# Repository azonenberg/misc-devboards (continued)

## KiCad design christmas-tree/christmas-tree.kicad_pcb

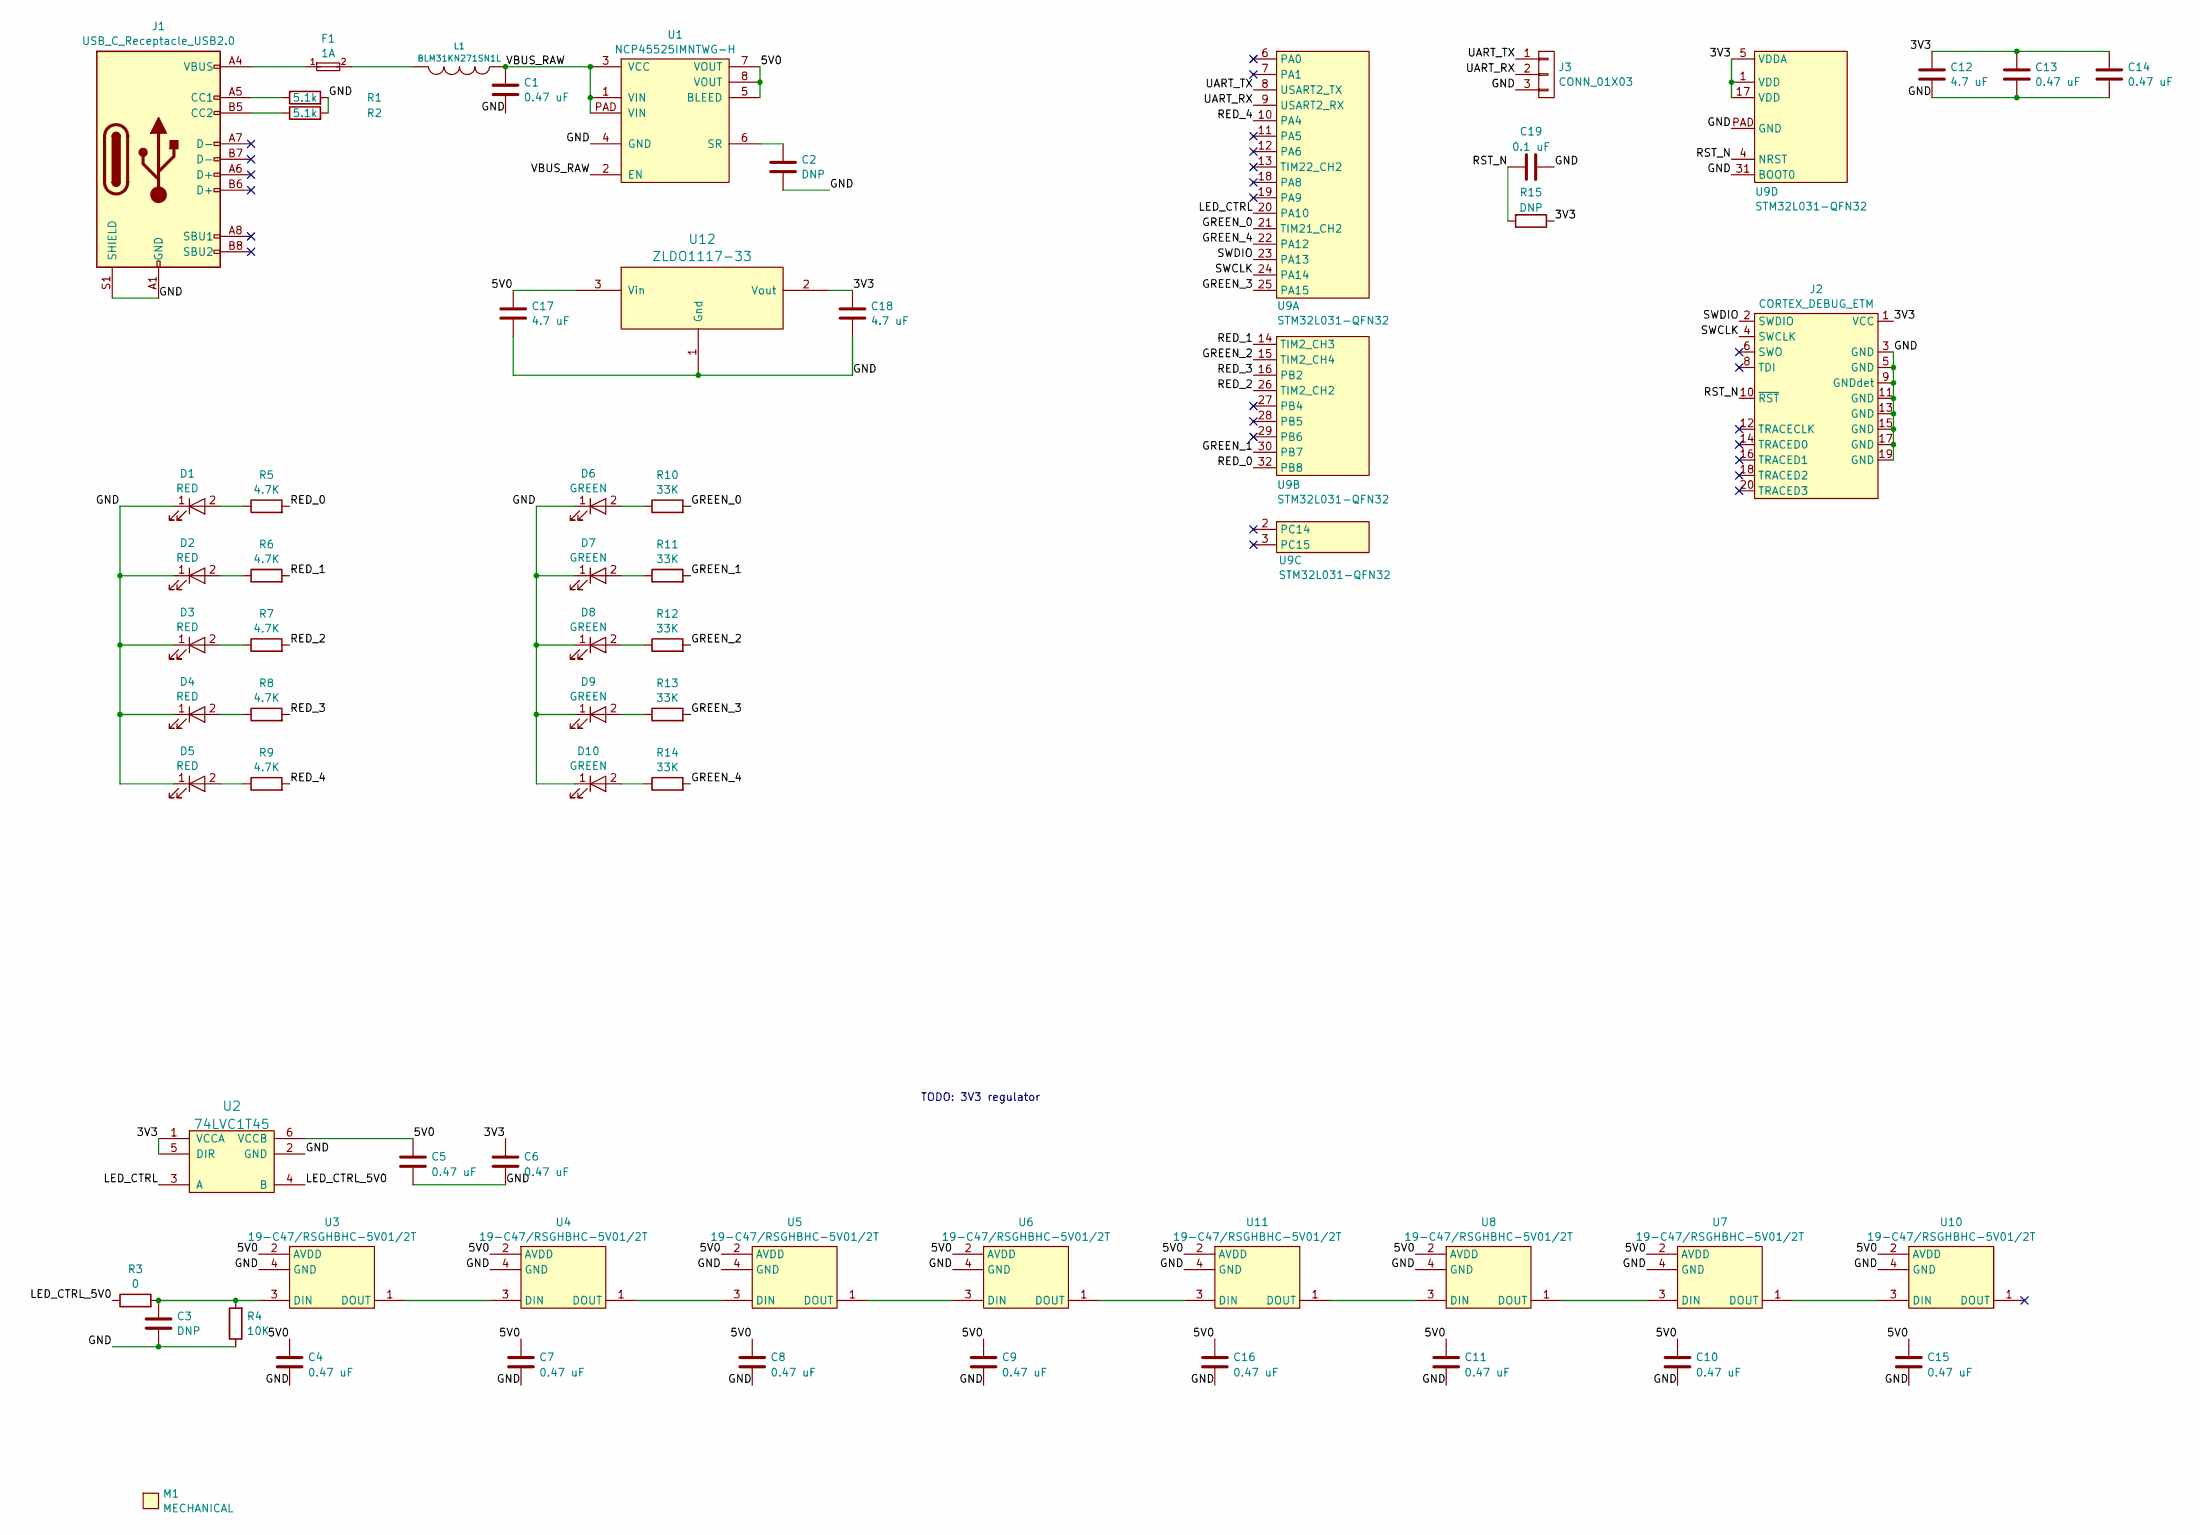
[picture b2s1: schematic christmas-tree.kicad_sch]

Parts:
C1, C4, C5, C6, C7, C8, C9, C10, C11, C13, C14, C15, C16: 0.47 uF; EIA_0402_CAP_NOSILK
C2, C3: DNP; EIA_0402_CAP_NOSILK
C12, C17, C18: 4.7 uF; EIA_0603_CAP_NOSILK
C19: 0.1 uF; EIA_0402_CAP_NOSILK
D1, D2, D3, D4, D5: RED; EIA_0402_LED
D6, D7, D8, D9, D10: GREEN; EIA_0402_LED
F1: 1A; EIA_0402_RES_NOSILK
J1: USB_C_Receptacle_USB2.0; USB_C_Receptacle_HRO_TYPE-C-31-M-12
J2: CORTEX_DEBUG_ETM; CONN_HEADER_1.27MM_2x10_SMT_SAMTEC_FTSH-110-01-L-DV-K
J3: CONN_01X03; CONN_HEADER_2.54MM_1x3_REFLOW
L1: BLM31KN271SN1L; EIA_1206_CAP_NOSILK
M1: MECHANICAL; MECHANICAL_CLEARANCEHOLE_4_40
R1, R2: 5.1k; EIA_0402_RES_NOSILK
R3: 0; EIA_0402_RES_NOSILK
R4: 10K; EIA_0402_RES_NOSILK
R5, R6, R7, R8, R9: 4.7K; EIA_0402_RES_NOSILK
R10, R11, R12, R13, R14: 33K; EIA_0402_RES_NOSILK
R15: DNP; EIA_0402_RES_NOSILK
U1: NCP45525IMNTWG-H; DFN_8_0.5MM_2x2MM
U2: 74LVC1T45; DFN_6_0.5MM_1.6x1.6MM_TI_DPK
U3, U4, U5, U6, U7, U8, U10, U11: 19-C47/RSGHBHC-5V01/2T; LED_EVERLIGHT_19-C47_RSGHBHC-5V01_2T
U9: STM32L031-QFN32; QFN_32_0.5MM_5x5MM
U12: ZLDO1117-33; SOT223-4

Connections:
/3V3: C6.1, C12.1, C13.1, C14.1, C18.1, J2.1 (VCC), R15.1, U2.1 (VCCA), U2.5 (DIR), U9.1 (VDD), U9.5 (VDDA), U9.17 (VDD), U12.2 (Vout)
/5V0: C4.1, C5.1, C7.1, C8.1, C9.1, C10.1, C11.1, C15.1, C16.1, C17.1, U1.5 (BLEED), U1.7 (VOUT), U1.8 (VOUT), U2.6 (VCCB), U3.2 (AVDD), U4.2 (AVDD), U5.2 (AVDD), U6.2 (AVDD), U7.2 (AVDD), U8.2 (AVDD), U10.2 (AVDD), U11.2 (AVDD), U12.3 (Vin)
/GND: C1.2, C2.2, C3.2, C4.2, C5.2, C6.2, C7.2, C8.2, C9.2, C10.2, C11.2, C12.2, C13.2, C14.2, C15.2, C16.2, C17.2, C18.2, C19.2, D1.1 (K), D2.1 (K), D3.1 (K), D4.1 (K), D5.1 (K), D6.1 (K), D7.1 (K), D8.1 (K), D9.1 (K), D10.1 (K), J1.A1 (GND), J1.A12 (GND), J1.B1 (GND), J1.B12 (GND), J1.S1 (SHIELD), J2.3 (GND), J2.5 (GND), J2.9 (GNDdet), J2.11 (GND), J2.13 (GND), J2.15 (GND), J2.17 (GND), J2.19 (GND), J3.3, R1.2, R2.2, R4.1, U1.4 (GND), U2.2 (GND), U3.4 (GND), U4.4 (GND), U5.4 (GND), U6.4 (GND), U7.4 (GND), U8.4 (GND), U9.31 (BOOT0), U9.PAD (GND), U10.4 (GND), U11.4 (GND), U12.1 (Gnd)
/GREEN_0: R10.2, U9.21 (TIM21_CH2)
/GREEN_1: R11.2, U9.30 (PB7)
/GREEN_2: R12.2, U9.15 (TIM2_CH4)
/GREEN_3: R13.2, U9.25 (PA15)
/GREEN_4: R14.2, U9.22 (PA12)
/LED_CTRL: U2.3 (A), U9.20 (PA10)
/LED_CTRL_5V0: R3.1, U2.4 (B)
/RED_0: R5.2, U9.32 (PB8)
/RED_1: R6.2, U9.14 (TIM2_CH3)
/RED_2: R7.2, U9.26 (TIM2_CH2)
/RED_3: R8.2, U9.16 (PB2)
/RED_4: R9.2, U9.10 (PA4)
/RST_N: C19.1, J2.10 (~RST), R15.2, U9.4 (NRST)
/SWCLK: J2.4 (SWCLK), U9.24 (PA14)
/SWDIO: J2.2 (SWDIO), U9.23 (PA13)
/UART_RX: J3.2, U9.9 (USART2_RX)
/UART_TX: J3.1, U9.8 (USART2_TX)
/VBUS_RAW: C1.1, L1.1, U1.1 (VIN), U1.2 (EN), U1.3 (VCC), U1.PAD (VIN)
unnamed: D1.2 (A), R5.1
unnamed: D2.2 (A), R6.1
unnamed: D3.2 (A), R7.1
unnamed: D4.2 (A), R8.1
unnamed: D5.2 (A), R9.1
unnamed: D6.2 (A), R10.1
unnamed: D7.2 (A), R11.1
unnamed: D8.2 (A), R12.1
unnamed: D9.2 (A), R13.1
unnamed: D10.2 (A), R14.1
unnamed: F1.1, J1.A4 (VBUS), J1.A9 (VBUS), J1.B4 (VBUS), J1.B9 (VBUS)
unnamed: F1.2, L1.2
unnamed: J1.A5 (CC1), R1.1
unnamed: J1.B5 (CC2), R2.1
unnamed: C2.1, U1.6 (SR)
unnamed: C3.1, R3.2, R4.2, U3.3 (DIN)
unnamed: U3.1 (DOUT), U4.3 (DIN)
unnamed: U4.1 (DOUT), U5.3 (DIN)
unnamed: U5.1 (DOUT), U6.3 (DIN)
unnamed: U7.3 (DIN), U8.1 (DOUT)
unnamed: U7.1 (DOUT), U10.3 (DIN)
unnamed: U6.1 (DOUT), U11.3 (DIN)
unnamed: U8.3 (DIN), U11.1 (DOUT)

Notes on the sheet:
TODO: 3V3 regulator

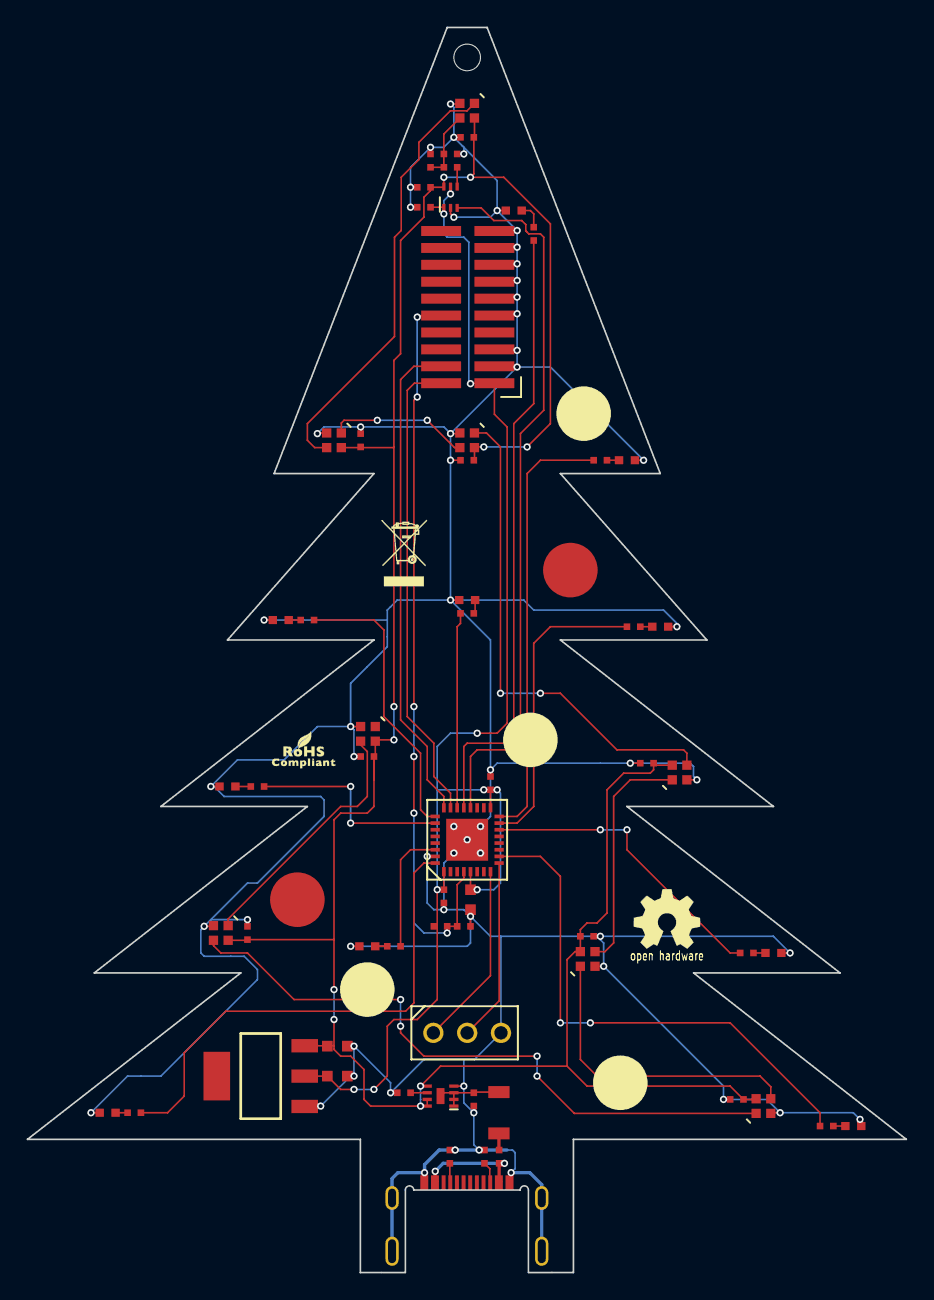
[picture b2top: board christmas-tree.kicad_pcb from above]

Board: 2 copper layers, 66.0 x 93.5 mm, 62 parts (0 on the bottom side), 44 nets.

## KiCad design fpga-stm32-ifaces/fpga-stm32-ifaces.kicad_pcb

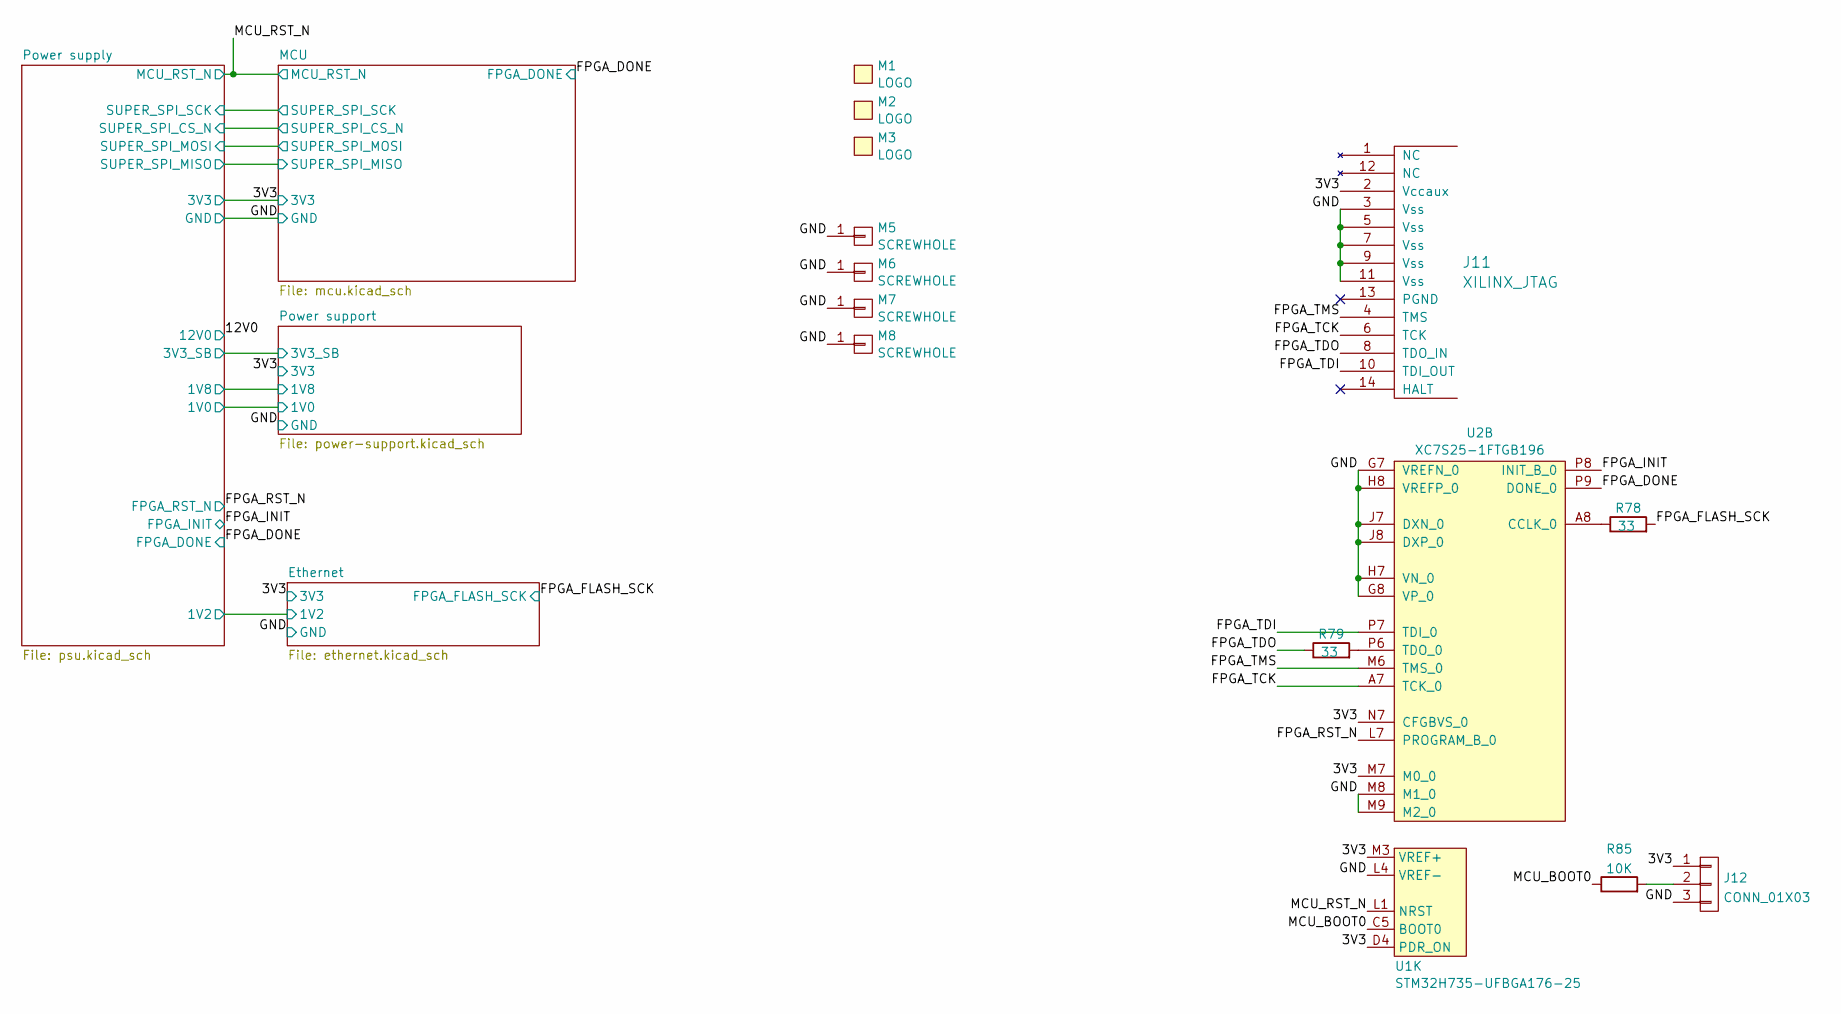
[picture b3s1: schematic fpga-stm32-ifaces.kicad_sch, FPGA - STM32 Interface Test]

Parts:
J11: XILINX_JTAG; XILINX_JTAG_PTH_MOLEX_0878311420
J12: CONN_01X03; CONN_HEADER_2.54MM_1x3
M1: LOGO; LONGTHING-1200DPI
M2: LOGO; Logo_silk_OSHW_6x6mm
M3: LOGO; Logo_silk_WEEE_3.4x5mm
M5, M6, M7, M8: SCREWHOLE; MECHANICAL_CLEARANCEHOLE_4_40
R78, R79: 33; EIA_0402_RES_NOSILK
R85: 10K; EIA_0402_RES_NOSILK
U1: STM32H735-UFBGA176-25; BGA_201_10x10_DEPOP_0.65MM_OSHPARK
U2: XC7S25-1FTGB196; BGA_196_15x15_FULLARRAY_1MM_FTGB196

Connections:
/3V3: J11.2 (Vccaux), J12.1, U1.D4 (PDR_ON), U1.M3 (VREF+), U2.M7 (M0_0), U2.N7 (CFGBVS_0); also elsewhere on the board
/FPGA_DONE: U2.P9 (DONE_0); also elsewhere on the board
/FPGA_FLASH_SCK: R78.2; also elsewhere on the board
/FPGA_INIT: U2.P8 (INIT_B_0); also elsewhere on the board
/FPGA_RST_N: U2.L7 (PROGRAM_B_0); also elsewhere on the board
/FPGA_TCK: J11.6 (TCK), U2.A7 (TCK_0)
/FPGA_TDI: J11.10 (TDI_OUT), U2.P7 (TDI_0)
/FPGA_TDO: J11.8 (TDO_IN), R79.1
/FPGA_TMS: J11.4 (TMS), U2.M6 (TMS_0)
/GND: J11.3 (Vss), J11.5 (Vss), J11.7 (Vss), J11.9 (Vss), J11.11 (Vss), J12.3, M5.1, M6.1, M7.1, M8.1, U1.L4 (VREF-), U2.G7 (VREFN_0), U2.G8 (VP_0), U2.H7 (VN_0), U2.H8 (VREFP_0), U2.J7 (DXN_0), U2.J8 (DXP_0), U2.M8 (M1_0), U2.M9 (M2_0); also elsewhere on the board
/MCU_BOOT0: R85.1, U1.C5 (BOOT0)
/MCU_RST_N: U1.L1 (NRST); also elsewhere on the board
unnamed: J12.2, R85.2
unnamed: R78.1, U2.A8 (CCLK_0)
unnamed: R79.2, U2.P6 (TDO_0)

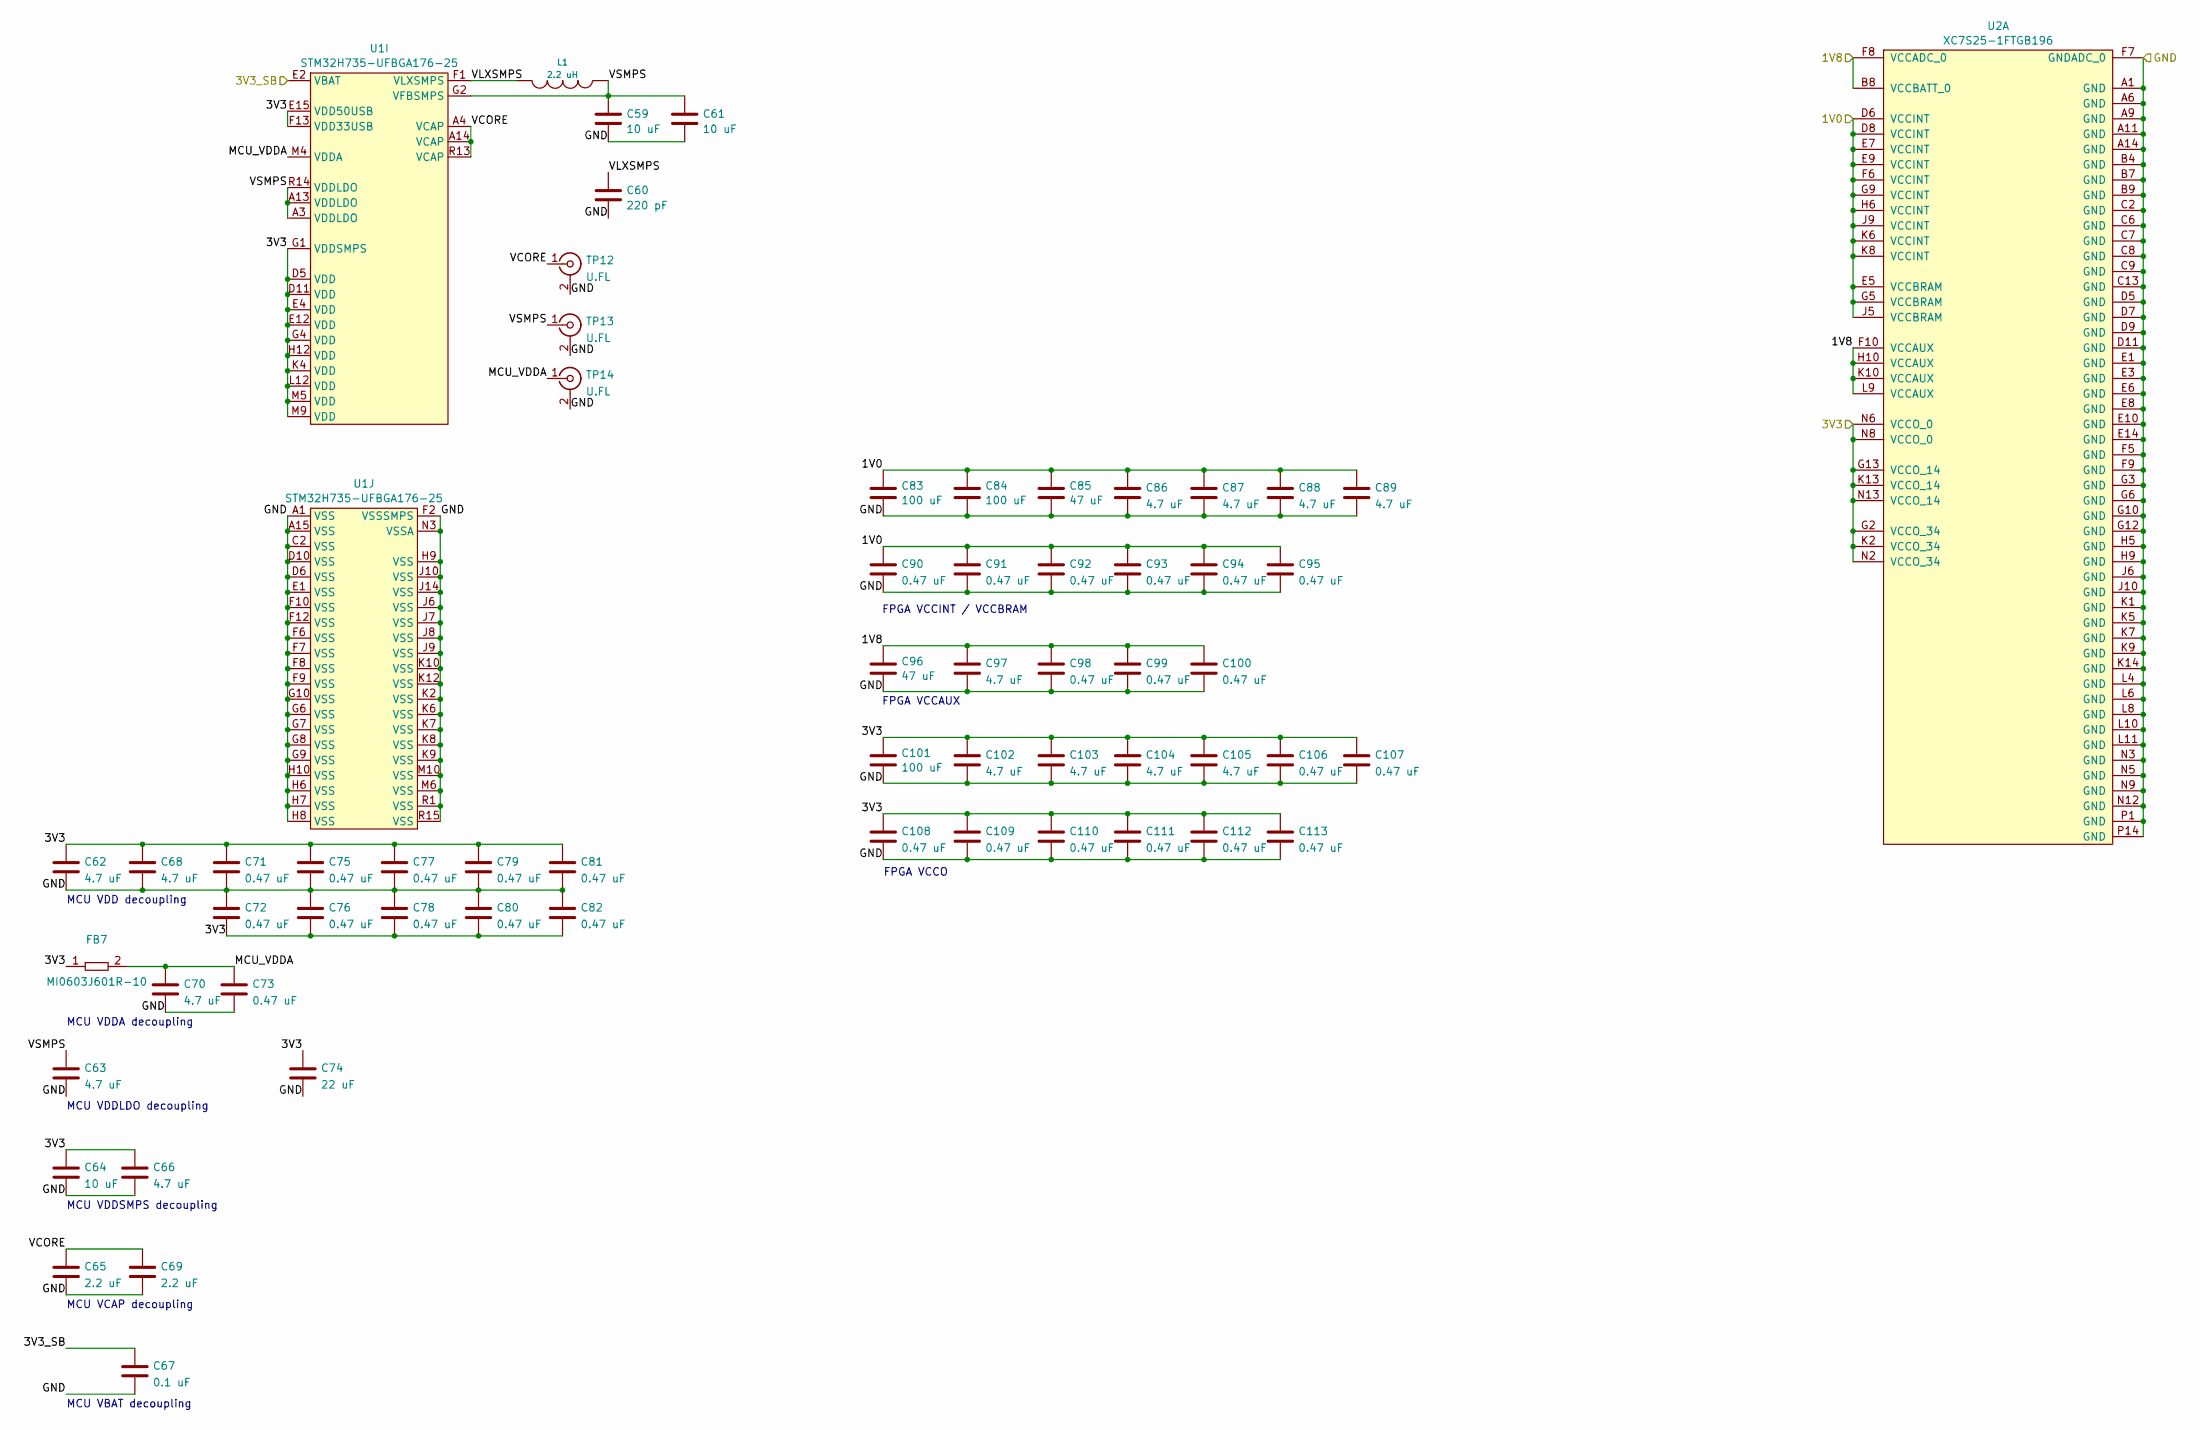
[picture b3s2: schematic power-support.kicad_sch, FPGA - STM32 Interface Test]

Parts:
C59, C61, C64: 10 uF; EIA_0805_CAP_NOSILK
C60: 220 pF; EIA_0402_CAP_NOSILK
C62, C63, C66, C68, C70, C86, C87, C88, C89, C97, C102, C103, C104, C105: 4.7 uF; EIA_0603_CAP_NOSILK
C65, C69: 2.2 uF; EIA_0805_CAP_NOSILK
C67: 0.1 uF; EIA_0402_CAP_NOSILK
C71, C72, C73, C75, C76, C77, C78, C79, C80, C81, C82, C90, C91, C92, C93, C94, C95, C98, C99, C100, C106, C107, C108, C109, C110, C111, C112, C113: 0.47 uF; EIA_0402_CAP_NOSILK
C74: 22 uF; EIA_0805_CAP_NOSILK
C83, C84, C101: 100 uF; EIA_1210_CAP_NOSILK
C85, C96: 47 uF; EIA_1210_CAP_NOSILK
FB7: MI0603J601R-10; EIA_0603_INDUCTOR_NOSILK
L1: 2.2 uH; EIA_1210_CAP_NOSILK
TP12, TP13, TP14: U.FL; CONN_U.FL_TE_1909763-1
U1: STM32H735-UFBGA176-25; BGA_201_10x10_DEPOP_0.65MM_OSHPARK
U2: XC7S25-1FTGB196; BGA_196_15x15_FULLARRAY_1MM_FTGB196

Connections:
/3V3: C62.1, C64.1, C66.1, C68.1, C71.1, C72.2, C74.1, C75.1, C76.2, C77.1, C78.2, C79.1, C80.2, C81.1, C82.2, C101.1, C102.1, C103.1, C104.1, C105.1, C106.1, C107.1, C108.1, C109.1, C110.1, C111.1, C112.1, C113.1, FB7.1, U1.D5 (VDD), U1.D11 (VDD), U1.E4 (VDD), U1.E12 (VDD), U1.E15 (VDD50USB), U1.F13 (VDD33USB), U1.G1 (VDDSMPS), U1.G4 (VDD), U1.H12 (VDD), U1.K4 (VDD), U1.L12 (VDD), U1.M5 (VDD), U1.M9 (VDD), U2.G2 (VCCO_34), U2.G13 (VCCO_14), U2.K2 (VCCO_34), U2.K13 (VCCO_14), U2.N2 (VCCO_34), U2.N6 (VCCO_0), U2.N8 (VCCO_0), U2.N13 (VCCO_14); also elsewhere on the board
/GND: C59.2, C60.2, C61.2, C62.2, C63.2, C64.2, C65.2, C66.2, C67.2, C68.2, C69.2, C70.2, C71.2, C72.1, C73.2, C74.2, C75.2, C76.1, C77.2, C78.1, C79.2, C80.1, C81.2, C82.1, C83.2, C84.2, C85.2, C86.2, C87.2, C88.2, C89.2, C90.2, C91.2, C92.2, C93.2, C94.2, C95.2, C96.2, C97.2, C98.2, C99.2, C100.2, C101.2, C102.2, C103.2, C104.2, C105.2, C106.2, C107.2, C108.2, C109.2, C110.2, C111.2, C112.2, C113.2, TP12.2 (Ext), TP13.2 (Ext), TP14.2 (Ext), U1.A1 (VSS), U1.A15 (VSS), U1.C2 (VSS), U1.D6 (VSS), U1.D10 (VSS), U1.E1 (VSS), U1.F2 (VSSSMPS), U1.F6 (VSS), U1.F7 (VSS), U1.F8 (VSS), U1.F9 (VSS), U1.F10 (VSS), U1.F12 (VSS), U1.G6 (VSS), U1.G7 (VSS), U1.G8 (VSS), U1.G9 (VSS), U1.G10 (VSS), U1.H6 (VSS), U1.H7 (VSS), U1.H8 (VSS), U1.H9 (VSS), U1.H10 (VSS), U1.J6 (VSS), U1.J7 (VSS), U1.J8 (VSS), U1.J9 (VSS), U1.J10 (VSS), U1.J14 (VSS), U1.K2 (VSS), U1.K6 (VSS), U1.K7 (VSS), U1.K8 (VSS), U1.K9 (VSS), U1.K10 (VSS), U1.K12 (VSS), U1.M6 (VSS), U1.M10 (VSS), U1.N3 (VSSA), U1.R1 (VSS), U1.R15 (VSS), U2.A1 (GND), U2.A6 (GND), U2.A9 (GND), U2.A11 (GND), U2.A14 (GND), U2.B4 (GND), U2.B7 (GND), U2.B9 (GND), U2.C2 (GND), U2.C6 (GND), U2.C7 (GND), U2.C8 (GND), U2.C9 (GND), U2.C13 (GND), U2.D5 (GND), U2.D7 (GND), U2.D9 (GND), U2.D11 (GND), U2.E1 (GND), U2.E3 (GND), U2.E6 (GND), U2.E8 (GND), U2.E10 (GND), U2.E14 (GND), U2.F5 (GND), U2.F7 (GNDADC_0), U2.F9 (GND), U2.G3 (GND), U2.G6 (GND), U2.G10 (GND), U2.G12 (GND), U2.H5 (GND), U2.H9 (GND), U2.J6 (GND), U2.J10 (GND), U2.K1 (GND), U2.K5 (GND), U2.K7 (GND), U2.K9 (GND), U2.K14 (GND), U2.L4 (GND), U2.L6 (GND), U2.L8 (GND), U2.L10 (GND), U2.L11 (GND), U2.N3 (GND), U2.N5 (GND), U2.N9 (GND), U2.N12 (GND), U2.P1 (GND), U2.P14 (GND); also elsewhere on the board
/Power supply/1V0: C83.1, C84.1, C85.1, C86.1, C87.1, C88.1, C89.1, C90.1, C91.1, C92.1, C93.1, C94.1, C95.1, U2.D6 (VCCINT), U2.D8 (VCCINT), U2.E5 (VCCBRAM), U2.E7 (VCCINT), U2.E9 (VCCINT), U2.F6 (VCCINT), U2.G5 (VCCBRAM), U2.G9 (VCCINT), U2.H6 (VCCINT), U2.J5 (VCCBRAM), U2.J9 (VCCINT), U2.K6 (VCCINT), U2.K8 (VCCINT); also elsewhere on the board
/Power supply/1V8: C96.1, C97.1, C98.1, C99.1, C100.1, U2.B8 (VCCBATT_0), U2.F8 (VCCADC_0), U2.F10 (VCCAUX), U2.H10 (VCCAUX), U2.K10 (VCCAUX), U2.L9 (VCCAUX); also elsewhere on the board
/Power supply/3V3_SB: C67.1, U1.E2 (VBAT); also elsewhere on the board
/Power support/MCU_VDDA: C70.1, C73.1, FB7.2, TP14.1 (In), U1.M4 (VDDA)
/Power support/VCORE: C65.1, C69.1, TP12.1 (In), U1.A4 (VCAP), U1.A14 (VCAP), U1.R13 (VCAP)
/Power support/VLXSMPS: C60.1, L1.2, U1.F1 (VLXSMPS)
/Power support/VSMPS: C59.1, C61.1, C63.1, L1.1, TP13.1 (In), U1.A3 (VDDLDO), U1.A13 (VDDLDO), U1.G2 (VFBSMPS), U1.R14 (VDDLDO)

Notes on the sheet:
FPGA VCCO
MCU VDDSMPS decoupling
MCU VCAP decoupling
MCU VBAT decoupling
FPGA VCCINT / VCCBRAM
MCU VDDLDO decoupling
FPGA VCCAUX
MCU VDD decoupling
MCU VDDA decoupling

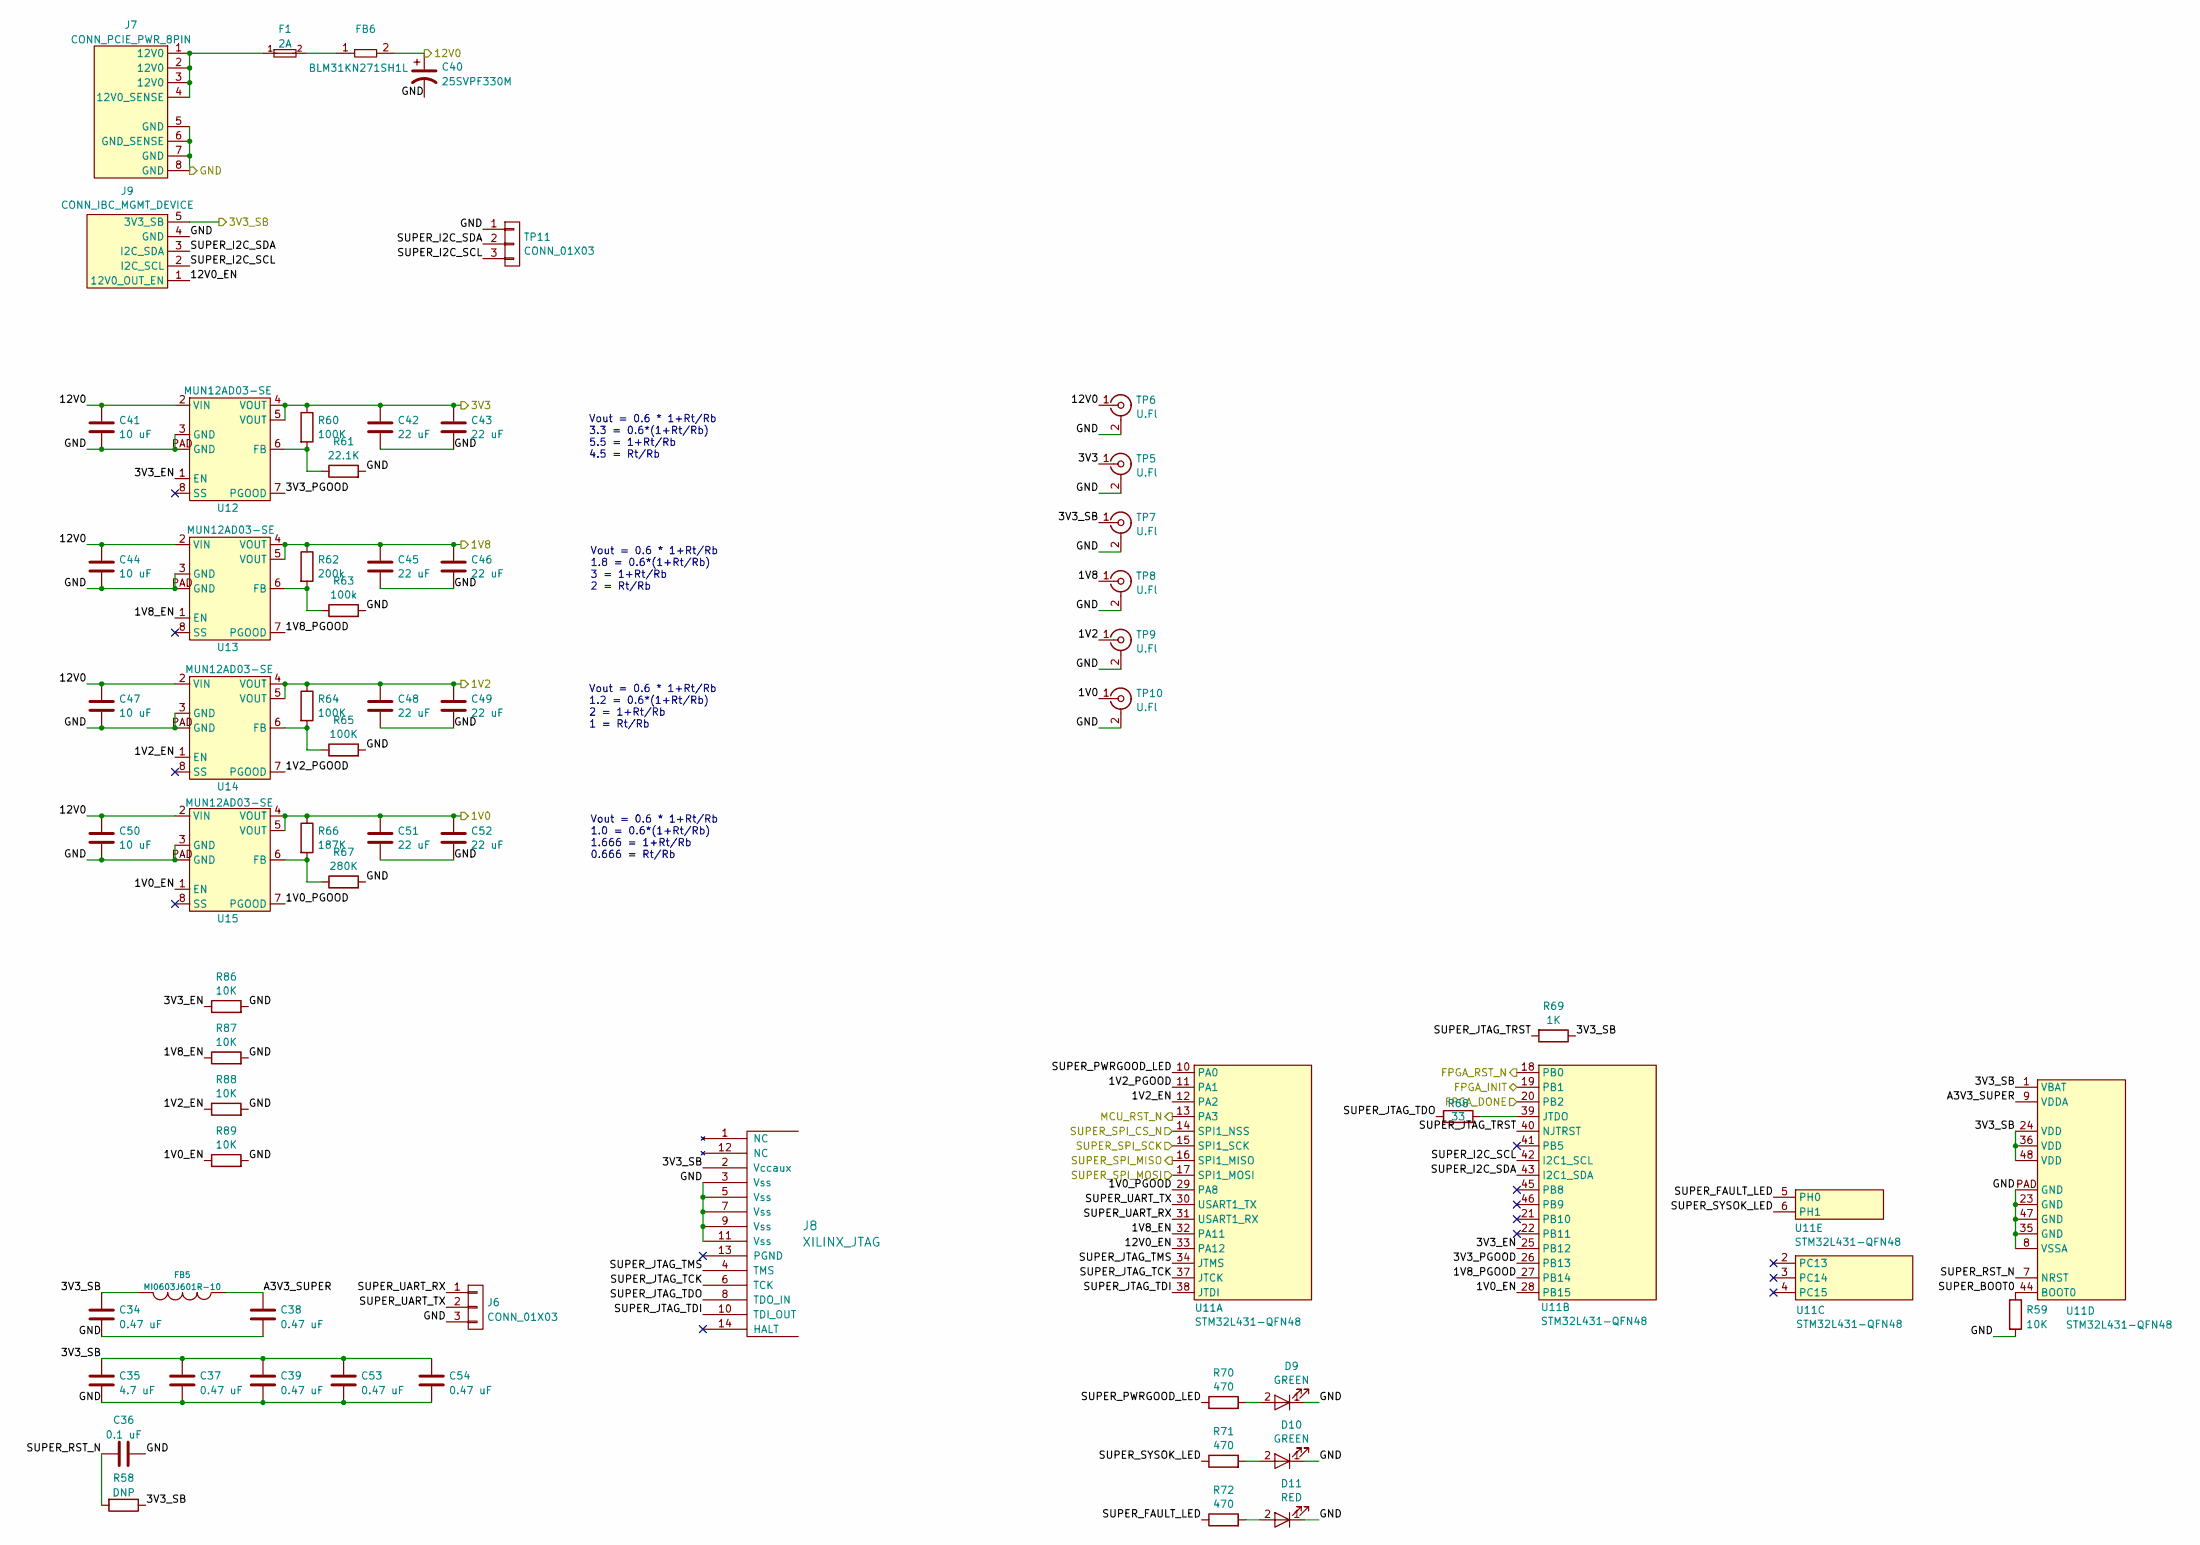
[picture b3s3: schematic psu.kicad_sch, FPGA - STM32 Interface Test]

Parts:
C34, C37, C38, C39, C53, C54: 0.47 uF; EIA_0402_CAP_NOSILK
C35: 4.7 uF; EIA_0603_CAP_NOSILK
C36: 0.1 uF; EIA_0402_CAP_NOSILK
C40: 25SVPF330M; CAP_AL_10MM_SMT
C41, C44, C47, C50: 10 uF; EIA_1210_CAP_NOSILK
C42, C43: 22 uF; EIA_1210_CAP_NOSILK
C45, C46, C48, C49, C51, C52: 22 uF; EIA_0805_CAP_NOSILK
D9, D10: GREEN; EIA_0603_LED
D11: RED; EIA_0603_LED
F1: 2A; EIA_0603_CAP_NOSILK
FB5: MI0603J601R-10; EIA_0603_INDUCTOR_NOSILK
FB6: BLM31KN271SH1L; EIA_1206_CAP_NOSILK
J6: CONN_01X03; CONN_HEADER_2.54MM_1x3
J7: CONN_PCIE_PWR_8PIN; CONN_MOLEX_MINIFITJR_8POS_0039291087
J8: XILINX_JTAG; XILINX_JTAG_PTH_MOLEX_0878311420
J9: CONN_IBC_MGMT_DEVICE; CONN_MOLEX_PICOBLADE_5POS_0532610571
R58: DNP; EIA_0402_RES_NOSILK
R59, R86, R87, R88, R89: 10K; EIA_0402_RES_NOSILK
R60, R64, R65: 100K; EIA_0402_RES_NOSILK
R61: 22.1K; EIA_0402_RES_NOSILK
R62: 200k; EIA_0402_RES_NOSILK
R63: 100k; EIA_0402_RES_NOSILK
R66: 187K; EIA_0402_RES_NOSILK
R67: 280K; EIA_0402_RES_NOSILK
R68: 33; EIA_0402_RES_NOSILK
R69: 1K; EIA_0402_RES_NOSILK
R70, R71, R72: 470; EIA_0402_RES_NOSILK
TP5, TP6, TP7, TP8, TP9, TP10: U.Fl; CONN_U.FL_TE_1909763-1
TP11: CONN_01X03; CONN_HEADER_2.54MM_1x3
U11: STM32L431-QFN48; QFN_48_0.5MM_7x7MM
U12, U13, U14, U15: MUN12AD03-SE; MODULE_CYNTEC_MUN12AD03-SE

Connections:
/3V3: C42.1, C43.1, R60.1, TP5.1 (In), U12.4 (VOUT), U12.5 (VOUT); also elsewhere on the board
/12V0: C40.1, C41.1, C44.1, C47.1, C50.1, FB6.2, TP6.1 (In), U12.2 (VIN), U13.2 (VIN), U14.2 (VIN), U15.2 (VIN)
/Ethernet/1V2: C48.1, C49.1, R64.1, TP9.1 (In), U14.4 (VOUT), U14.5 (VOUT); also elsewhere on the board
/FPGA_DONE: U11.20 (PB2); also elsewhere on the board
/FPGA_INIT: U11.19 (PB1); also elsewhere on the board
/FPGA_RST_N: U11.18 (PB0); also elsewhere on the board
/GND: C34.2, C35.2, C36.2, C37.2, C38.2, C39.2, C40.2, C41.2, C42.2, C43.2, C44.2, C45.2, C46.2, C47.2, C48.2, C49.2, C50.2, C51.2, C52.2, C53.2, C54.2, D9.1 (K), D10.1 (K), D11.1 (K), J6.3, J7.5 (GND), J7.6 (GND_SENSE), J7.7 (GND), J7.8 (GND), J8.3 (Vss), J8.5 (Vss), J8.7 (Vss), J8.9 (Vss), J8.11 (Vss), J9.4 (GND), R59.2, R61.2, R63.2, R65.2, R67.2, R86.2, R87.2, R88.2, R89.2, TP5.2 (Ext), TP6.2 (Ext), TP7.2 (Ext), TP8.2 (Ext), TP9.2 (Ext), TP10.2 (Ext), TP11.1, U11.8 (VSSA), U11.23 (GND), U11.35 (GND), U11.47 (GND), U11.PAD (GND), U12.3 (GND), U12.PAD (GND), U13.3 (GND), U13.PAD (GND), U14.3 (GND), U14.PAD (GND), U15.3 (GND), U15.PAD (GND); also elsewhere on the board
/MCU/SUPER_SPI_CS_N: U11.14 (SPI1_NSS); also elsewhere on the board
/MCU/SUPER_SPI_MISO: U11.16 (SPI1_MISO); also elsewhere on the board
/MCU/SUPER_SPI_MOSI: U11.17 (SPI1_MOSI); also elsewhere on the board
/MCU/SUPER_SPI_SCK: U11.15 (SPI1_SCK); also elsewhere on the board
/MCU_RST_N: U11.13 (PA3); also elsewhere on the board
/Power supply/1V0: C51.1, C52.1, R66.1, TP10.1 (In), U15.4 (VOUT), U15.5 (VOUT); also elsewhere on the board
/Power supply/1V0_EN: R89.1, U11.28 (PB15), U15.1 (EN)
/Power supply/1V0_PGOOD: U11.29 (PA8), U15.7 (PGOOD)
/Power supply/1V2_EN: R88.1, U11.12 (PA2), U14.1 (EN)
/Power supply/1V2_PGOOD: U11.11 (PA1), U14.7 (PGOOD)
/Power supply/1V8: C45.1, C46.1, R62.1, TP8.1 (In), U13.4 (VOUT), U13.5 (VOUT); also elsewhere on the board
/Power supply/1V8_EN: R87.1, U11.32 (PA11), U13.1 (EN)
/Power supply/1V8_PGOOD: U11.27 (PB14), U13.7 (PGOOD)
/Power supply/3V3_EN: R86.1, U11.25 (PB12), U12.1 (EN)
/Power supply/3V3_PGOOD: U11.26 (PB13), U12.7 (PGOOD)
/Power supply/3V3_SB: C34.1, C35.1, C37.1, C39.1, C53.1, C54.1, FB5.2, J8.2 (Vccaux), J9.5 (3V3_SB), R58.1, R69.1, TP7.1 (In), U11.1 (VBAT), U11.24 (VDD), U11.36 (VDD), U11.48 (VDD); also elsewhere on the board
/Power supply/12V0_EN: J9.1 (12V0_OUT_EN), U11.33 (PA12)
/Power supply/A3V3_SUPER: C38.1, FB5.1, U11.9 (VDDA)
/Power supply/SUPER_BOOT0: R59.1, U11.44 (BOOT0)
/Power supply/SUPER_FAULT_LED: R72.1, U11.5 (PH0)
/Power supply/SUPER_I2C_SCL: J9.2 (I2C_SCL), TP11.3, U11.42 (I2C1_SCL)
/Power supply/SUPER_I2C_SDA: J9.3 (I2C_SDA), TP11.2, U11.43 (I2C1_SDA)
/Power supply/SUPER_JTAG_TCK: J8.6 (TCK), U11.37 (JTCK)
/Power supply/SUPER_JTAG_TDI: J8.10 (TDI_OUT), U11.38 (JTDI)
/Power supply/SUPER_JTAG_TDO: J8.8 (TDO_IN), R68.1
/Power supply/SUPER_JTAG_TMS: J8.4 (TMS), U11.34 (JTMS)
/Power supply/SUPER_JTAG_TRST: R69.2, U11.40 (NJTRST)
/Power supply/SUPER_PWRGOOD_LED: R70.1, U11.10 (PA0)
/Power supply/SUPER_RST_N: C36.1, R58.2, U11.7 (NRST)
/Power supply/SUPER_SYSOK_LED: R71.1, U11.6 (PH1)
/Power supply/SUPER_UART_RX: J6.1, U11.31 (USART1_RX)
/Power supply/SUPER_UART_TX: J6.2, U11.30 (USART1_TX)
unnamed: D9.2 (A), R70.2
unnamed: D10.2 (A), R71.2
unnamed: D11.2 (A), R72.2
unnamed: F1.2, FB6.1
unnamed: F1.1, J7.1 (12V0), J7.2 (12V0), J7.3 (12V0), J7.4 (12V0_SENSE)
unnamed: R68.2, U11.39 (JTDO)
unnamed: R60.2, R61.1, U12.6 (FB)
unnamed: R62.2, R63.1, U13.6 (FB)
unnamed: R64.2, R65.1, U14.6 (FB)
unnamed: R66.2, R67.1, U15.6 (FB)

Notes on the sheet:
Vout = 0.6 * 1+Rt/Rb 1.8 = 0.6*(1+Rt/Rb) 3 = 1+Rt/Rb 2 = Rt/Rb
Vout = 0.6 * 1+Rt/Rb 1.2 = 0.6*(1+Rt/Rb) 2 = 1+Rt/Rb 1 = Rt/Rb
Vout = 0.6 * 1+Rt/Rb 1.0 = 0.6*(1+Rt/Rb) 1.666 = 1+Rt/Rb 0.666 = Rt/Rb
Vout = 0.6 * 1+Rt/Rb 3.3 = 0.6*(1+Rt/Rb) 5.5 = 1+Rt/Rb 4.5 = Rt/Rb
